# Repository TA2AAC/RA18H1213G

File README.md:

# RA18H1213G
RA18H1213G Amplifier PCB Project

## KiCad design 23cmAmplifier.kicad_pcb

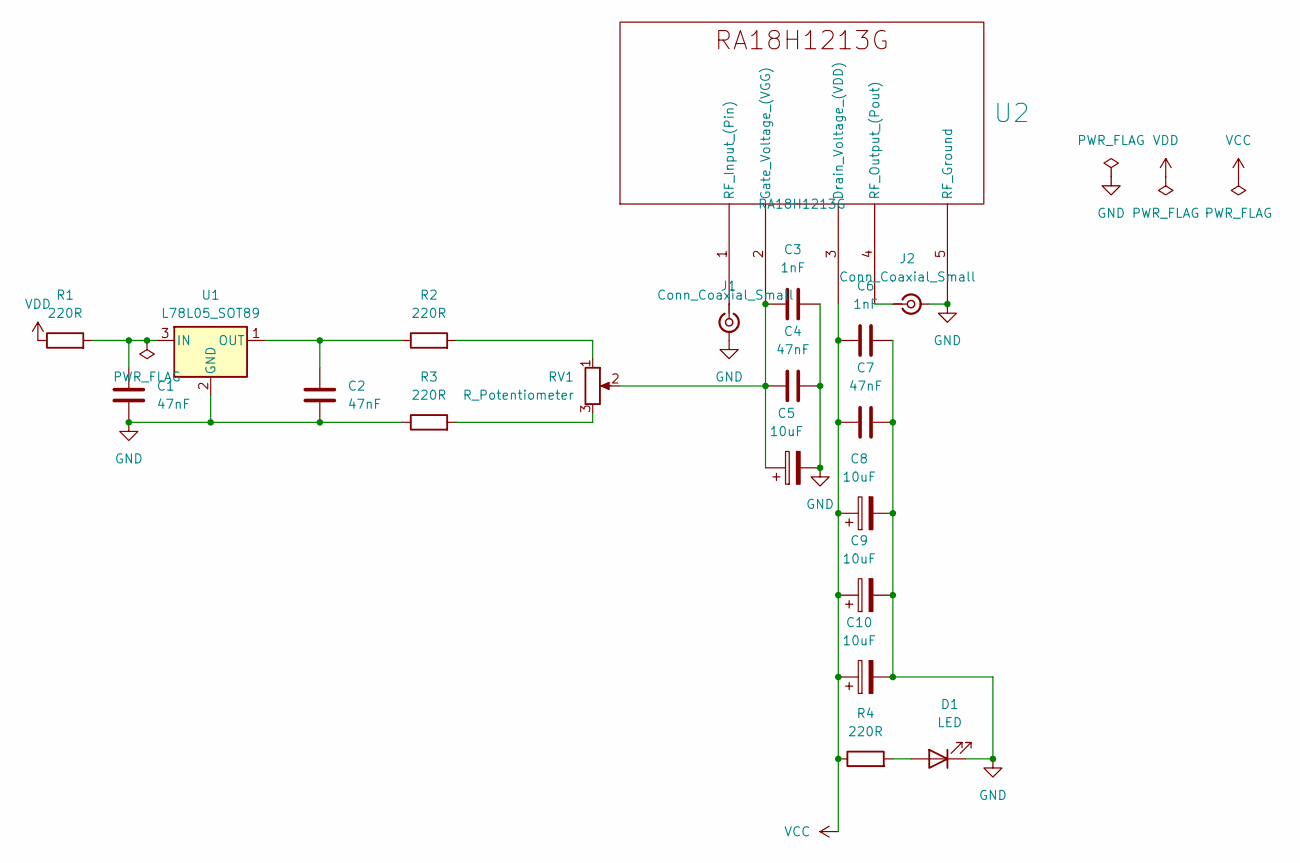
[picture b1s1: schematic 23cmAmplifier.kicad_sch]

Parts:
C1, C2, C4, C7: 47nF; C_0805_2012Metric_Pad1.18x1.45mm_HandSolder
C3, C6: 1nF; C_0805_2012Metric_Pad1.18x1.45mm_HandSolder
C5, C8, C9, C10: 10uF; CP_EIA-6032-28_Kemet-C_Pad2.25x2.35mm_HandSolder
D1: LED; R_1206_3216Metric_Pad1.30x1.75mm_HandSolder
J1, J2: Conn_Coaxial_Small; SMA_Amphenol_132289_EdgeMount
R1, R2, R3, R4: 220R; R_1206_3216Metric_Pad1.30x1.75mm_HandSolder
RV1: R_Potentiometer; Potentiometer_Bourns_3224G_Horizontal
U1: L78L05_SOT89; SOT-89-3
U2: RA18H1213G; RA18H1213G Module

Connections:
GND: C1.2, C2.2, C3.2, C4.2, C5.2, C6.2, C7.2, C8.2, C9.2, C10.2, D1.1 (K), J1.2 (Ext), J2.2 (Ext), R3.1, U1.2 (GND), U2.5 (RF_Ground)
unnamed: D1.2 (A), R4.2
unnamed: J1.1 (In), U2.1 (RF_Input_(Pin))
unnamed: J2.1 (In), U2.4 (RF_Output_(Pout))
unnamed: R2.2, RV1.1
unnamed: R3.2, RV1.3
unnamed: C1.1, R1.2, U1.3 (IN)
unnamed: C2.1, R2.1, U1.1 (OUT)
unnamed: C3.1, C4.1, C5.1, RV1.2, U2.2 (Gate_Voltage_(VGG))
VCC: C6.1, C7.1, C8.1, C9.1, C10.1, R4.1, U2.3 (Drain_Voltage_(VDD))
VDD: R1.1

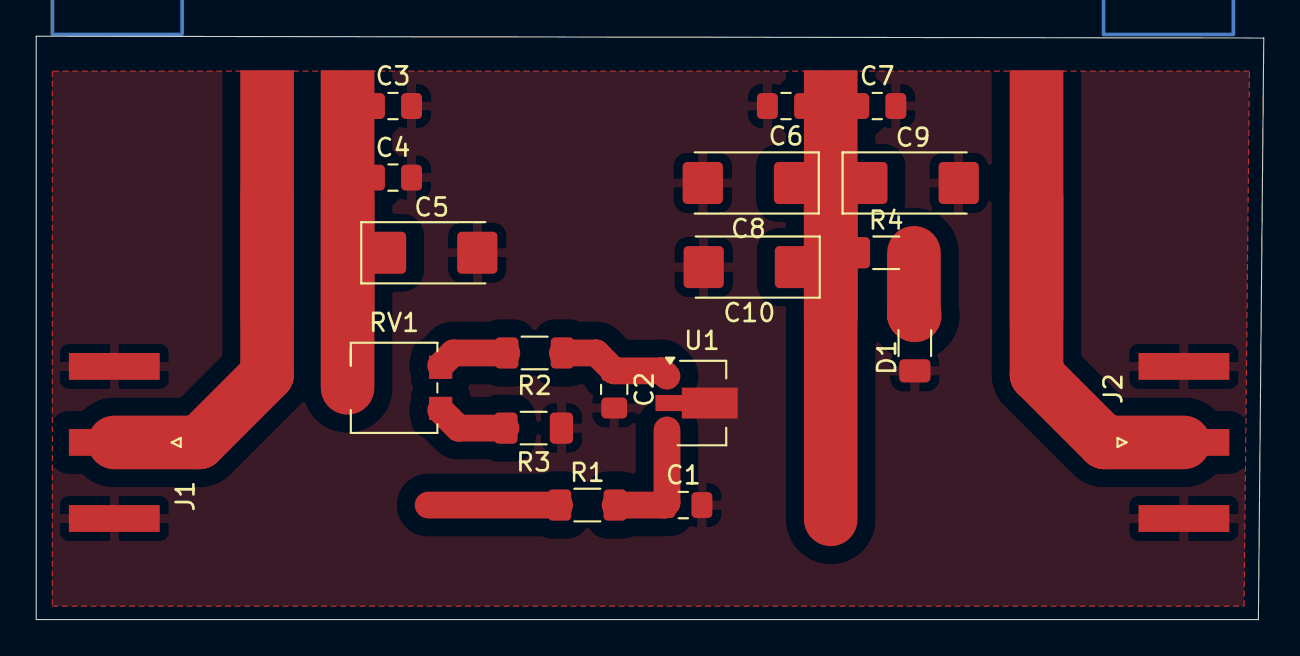
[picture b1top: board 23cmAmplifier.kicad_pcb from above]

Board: 2 copper layers, 68.6 x 32.6 mm, 20 parts (0 on the bottom side), 10 nets.
